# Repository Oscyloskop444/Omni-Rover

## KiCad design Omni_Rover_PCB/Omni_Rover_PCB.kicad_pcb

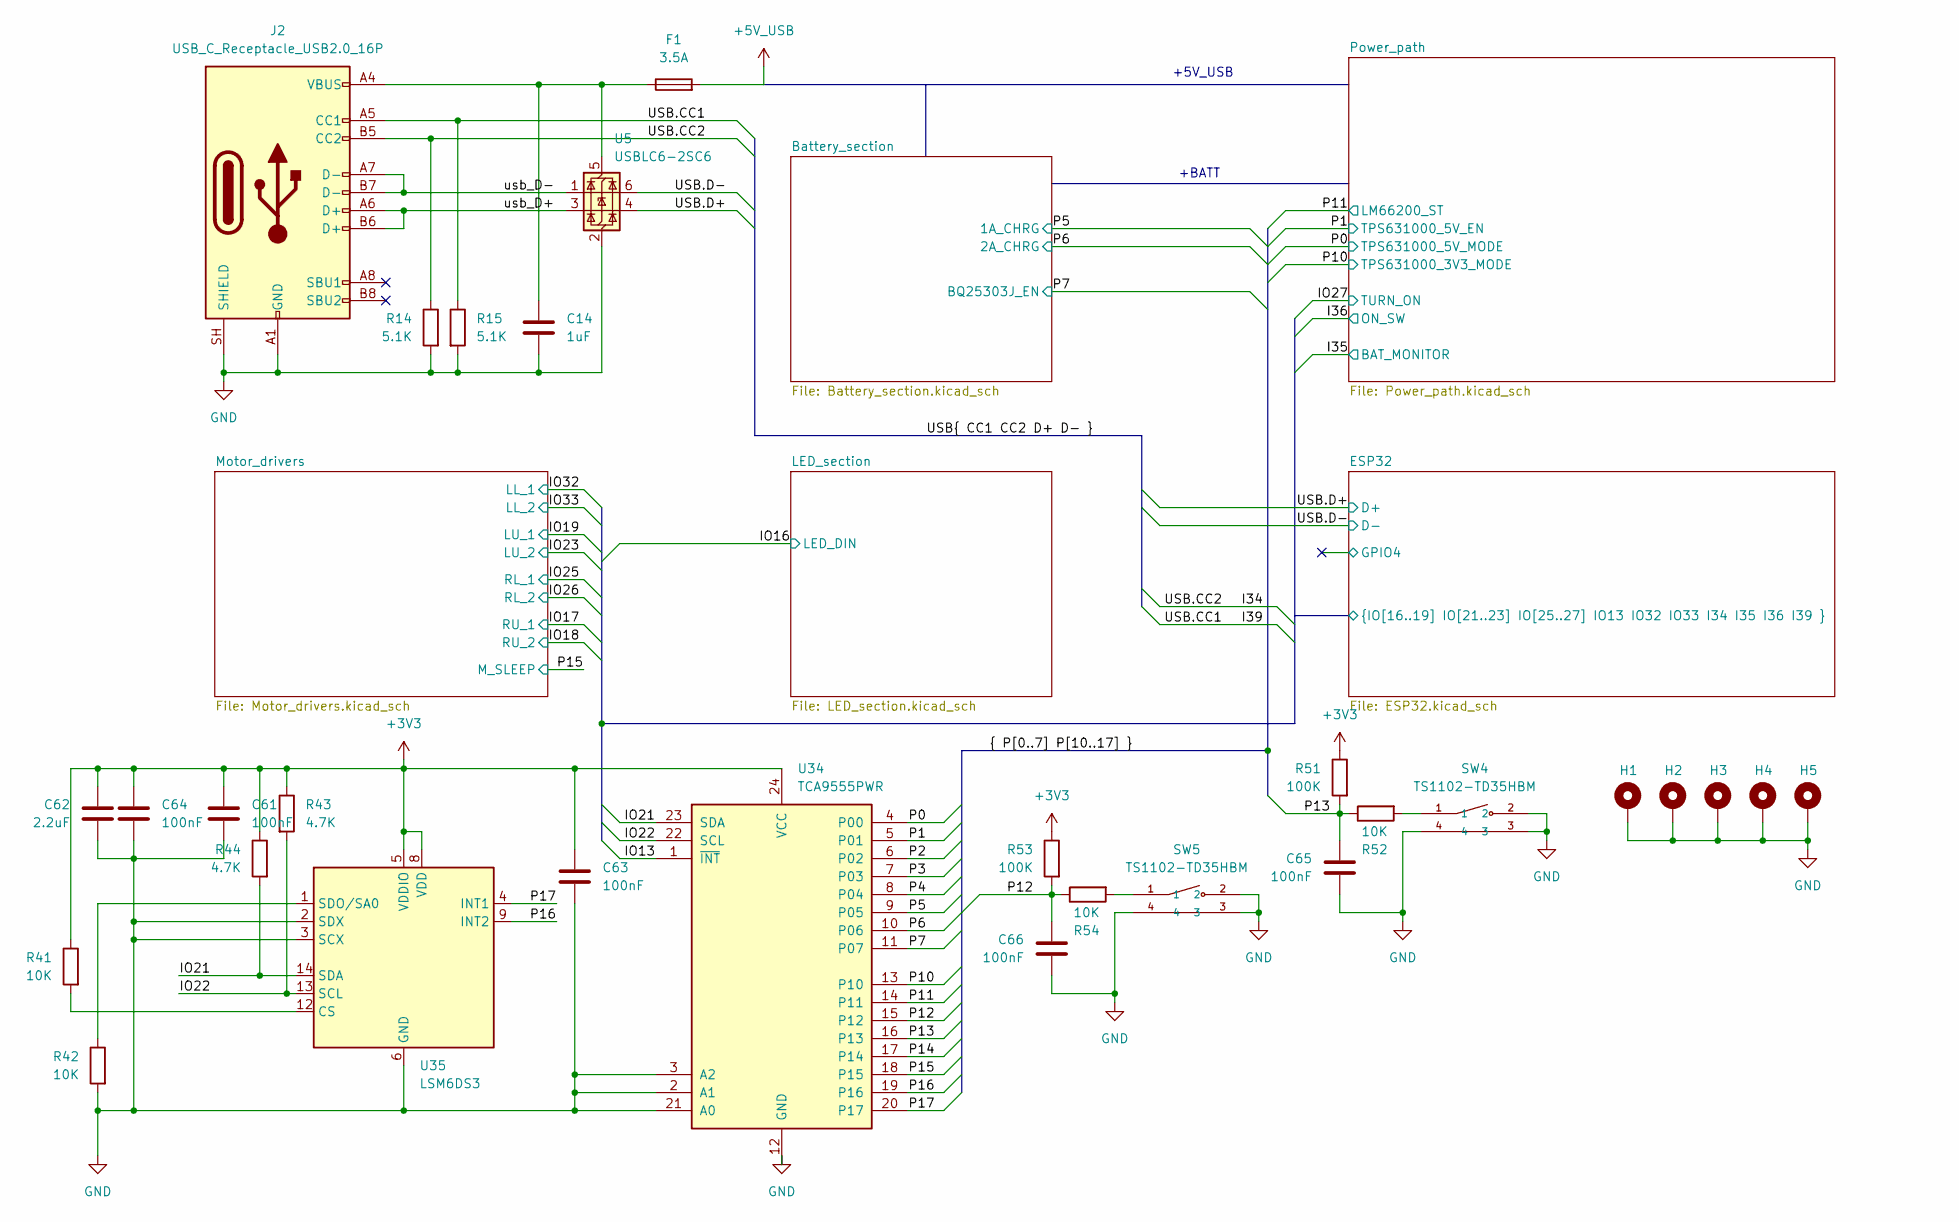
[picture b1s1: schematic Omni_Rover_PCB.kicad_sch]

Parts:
C14: 1uF; C_0603_1608Metric_Pad1.08x0.95mm_HandSolder
C61, C63, C64, C65, C66: 100nF; C_0402_1005Metric_Pad0.74x0.62mm_HandSolder
C62: 2.2uF; C_0402_1005Metric_Pad0.74x0.62mm_HandSolder
F1: 3.5A; Fuse_1206_3216Metric_Pad1.42x1.75mm_HandSolder
H1, H2, H3, H4, H5: MountingHole_Pad; MountingHole_3.2mm_M3_Pad_Via
J2: USB_C_Receptacle_USB2.0_16P; USB_C_Receptacle_GCT_USB4105-xx-A_16P_TopMnt_Horizontal
R14, R15: 5.1K; R_0402_1005Metric_Pad0.72x0.64mm_HandSolder
R41, R42, R52, R54: 10K; R_0402_1005Metric_Pad0.72x0.64mm_HandSolder
R43, R44: 4.7K; R_0402_1005Metric_Pad0.72x0.64mm_HandSolder
R51, R53: 100K; R_0402_1005Metric_Pad0.72x0.64mm_HandSolder
SW4, SW5: TS1102-TD35HBM; C36936640_SW-SMD_TS1102-TD35HBM; LCSC C36936640
U5: USBLC6-2SC6; SOT-23-6
U34: TCA9555PWR; TSSOP-24_4.4x7.8mm_P0.65mm
U35: LSM6DS3; LGA-14_3x2.5mm_P0.5mm_LayoutBorder3x4y

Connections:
+3V3: C61.2, C62.1, C63.2, C64.2, R41.1, R43.1, R44.1, R51.1, R53.1, U34.24 (VCC), U35.5 (VDDIO), U35.8 (VDD); also elsewhere on the board
+5V_USB: F1.2; also elsewhere on the board
/ESP32/I34: J2.B5 (CC2), R14.1; also elsewhere on the board
/ESP32/I39: J2.A5 (CC1), R15.1; also elsewhere on the board
/ESP32/IO13: U34.1 (~INT); also elsewhere on the board
/ESP32/IO21: R44.2, U34.23 (SDA), U35.14 (SDA); also elsewhere on the board
/ESP32/IO22: R43.2, U34.22 (SCL), U35.13 (SCL); also elsewhere on the board
/P0: U34.4 (P00); also elsewhere on the board
/P1: U34.5 (P01); also elsewhere on the board
/P2: U34.6 (P02)
/P3: U34.7 (P03)
/P4: U34.8 (P04)
/P5: U34.9 (P05); also elsewhere on the board
/P6: U34.10 (P06); also elsewhere on the board
/P7: U34.11 (P07); also elsewhere on the board
/P10: U34.13 (P10); also elsewhere on the board
/P11: U34.14 (P11); also elsewhere on the board
/P12: C66.2, R53.2, R54.1, U34.15 (P12)
/P13: C65.2, R51.2, R52.1, U34.16 (P13)
/P14: U34.17 (P14)
/P15: U34.18 (P15); also elsewhere on the board
/P16: U34.19 (P16), U35.9 (INT2)
/P17: U34.20 (P17), U35.4 (INT1)
/USB.D+: U5.4 (I/O2); also elsewhere on the board
/USB.D-: U5.6 (I/O1); also elsewhere on the board
/usb_D+: J2.A6 (D+), J2.B6 (D+), U5.3 (I/O2)
/usb_D-: J2.A7 (D-), J2.B7 (D-), U5.1 (I/O1)
GND: C14.2, C61.1, C62.2, C63.1, C64.1, C65.1, C66.1, H1.1 (1_1), H2.1 (1_1), H3.1 (1_1), H4.1 (1_1), H5.1 (1_1), J2.A1 (GND), J2.A12 (GND), J2.B1 (GND), J2.B12 (GND), J2.SH (SHIELD), R14.2, R15.2, R42.2, SW4.2, SW4.3, SW4.4, SW5.2, SW5.3, SW5.4, U5.2 (GND), U34.2 (A1), U34.3 (A2), U34.12 (GND), U34.21 (A0), U35.2 (SDX), U35.3 (SCX), U35.6 (GND), U35.7 (GND); also elsewhere on the board
unnamed: R52.2, SW4.1
unnamed: R54.2, SW5.1
unnamed: C14.1, F1.1, J2.A4 (VBUS), J2.A9 (VBUS), J2.B4 (VBUS), J2.B9 (VBUS), U5.5 (VBUS)
unnamed: R41.2, U35.12 (CS)
unnamed: R42.1, U35.1 (SDO/SA0)

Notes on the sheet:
+BATT
+5V_USB

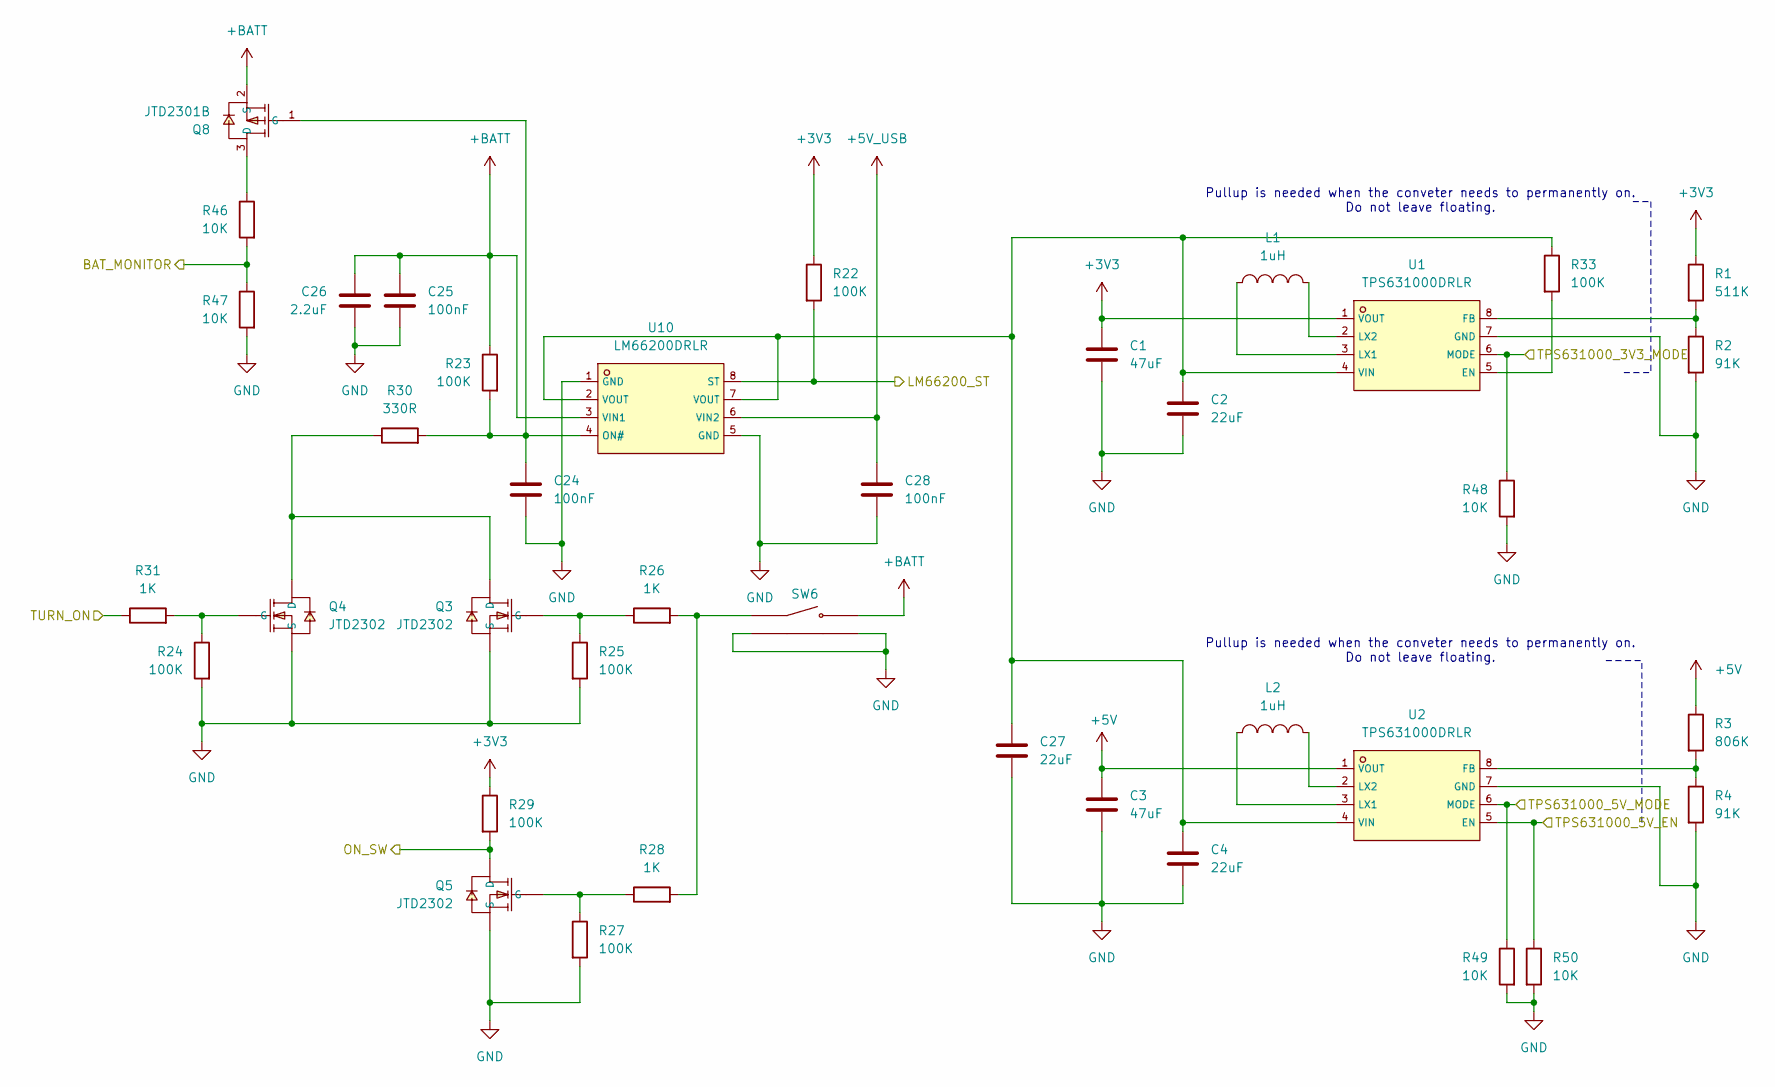
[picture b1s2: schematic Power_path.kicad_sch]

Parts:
C1, C3: 47uF; C_0805_2012Metric_Pad1.18x1.45mm_HandSolder
C2, C4: 22uF; C_0603_1608Metric_Pad1.08x0.95mm_HandSolder
C24, C25, C28: 100nF; C_0402_1005Metric_Pad0.74x0.62mm_HandSolder
C26: 2.2uF; C_0402_1005Metric_Pad0.74x0.62mm_HandSolder
C27: 22uF; C_0805_2012Metric_Pad1.18x1.45mm_HandSolder
L1, L2: 1uH; C882955_L1008; LCSC C882955
Q3, Q4, Q5: JTD2302; C42443455_SOT-23-3_L2_9-W1_5-P2_0-LS2_5-BR; LCSC C42443455
Q8: JTD2301B; C49308281_SOT-23-3_L2_9-W1_3-P1_90-LS2_4-BR; LCSC C49308281
R1: 511K; R_0402_1005Metric_Pad0.72x0.64mm_HandSolder
R2, R4: 91K; R_0402_1005Metric_Pad0.72x0.64mm_HandSolder
R3: 806K; R_0402_1005Metric_Pad0.72x0.64mm_HandSolder
R22, R23, R24, R25, R27, R29, R33: 100K; R_0402_1005Metric_Pad0.72x0.64mm_HandSolder
R26, R28, R31: 1K; R_0402_1005Metric_Pad0.72x0.64mm_HandSolder
R30: 330R; R_0402_1005Metric_Pad0.72x0.64mm_HandSolder
R46, R47, R48, R49, R50: 10K; R_0402_1005Metric_Pad0.72x0.64mm_HandSolder
SW6: TS1102-TD35HBM; C36936640_SW-SMD_TS1102-TD35HBM; LCSC C36936640
U1, U2: TPS631000DRLR; C5219190_SOT-583-8_L2_1-W1_2-P0_50-LS1_6-BL; LCSC C5219190
U10: LM66200DRLR; C3235556_SOT-583-8_L2_1-W1_2-P0_50-LS1_6-BL; LCSC C3235556

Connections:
+3V3: C1.1, R1.1, R22.1, R29.1, U1.1 (VOUT); also elsewhere on the board
+5V: C3.1, R3.1, U2.1 (VOUT); also elsewhere on the board
+5V_USB: C28.1, U10.6 (VIN2); also elsewhere on the board
+BATT: C25.1, C26.1, Q8.2 (S), R23.1, SW6.2, U10.3 (VIN1); also elsewhere on the board
/ESP32/I35: R46.2, R47.1; also elsewhere on the board
/ESP32/I36: Q5.3 (D), R29.2; also elsewhere on the board
/ESP32/IO27: R31.1; also elsewhere on the board
/P0: R49.1, U2.6 (MODE); also elsewhere on the board
/P1: R50.1, U2.5 (EN); also elsewhere on the board
/P10: R48.1, U1.6 (MODE); also elsewhere on the board
/P11: R22.2, U10.8 (ST); also elsewhere on the board
GND: C1.2, C2.2, C3.2, C4.2, C24.2, C25.2, C26.2, C27.2, C28.2, Q3.2 (S), Q4.2 (S), Q5.2 (S), R2.2, R4.2, R24.2, R25.2, R27.2, R47.2, R48.2, R49.2, R50.2, SW6.3, SW6.4, U1.7 (GND), U2.7 (GND), U10.1 (GND), U10.5 (GND); also elsewhere on the board
unnamed: Q3.3 (D), Q4.3 (D), R30.1
unnamed: Q3.1 (G), R25.1, R26.1
unnamed: Q4.1 (G), R24.1, R31.2
unnamed: Q5.1 (G), R27.1, R28.1
unnamed: Q8.3 (D), R46.1
unnamed: C24.1, Q8.1 (G), R23.2, R30.2, U10.4 (ON#)
unnamed: R26.2, R28.2, SW6.1
unnamed: R33.2, U1.5 (EN)
unnamed: R1.2, R2.1, U1.8 (FB)
unnamed: L1.1, U1.3 (LX1)
unnamed: L1.2, U1.2 (LX2)
unnamed: C2.1, C4.1, C27.1, R33.1, U1.4 (VIN), U2.4 (VIN), U10.2 (VOUT), U10.7 (VOUT)
unnamed: R3.2, R4.1, U2.8 (FB)
unnamed: L2.1, U2.3 (LX1)
unnamed: L2.2, U2.2 (LX2)

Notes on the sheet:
Pullup is needed when the conveter needs to permanently on. Do not leave floating.

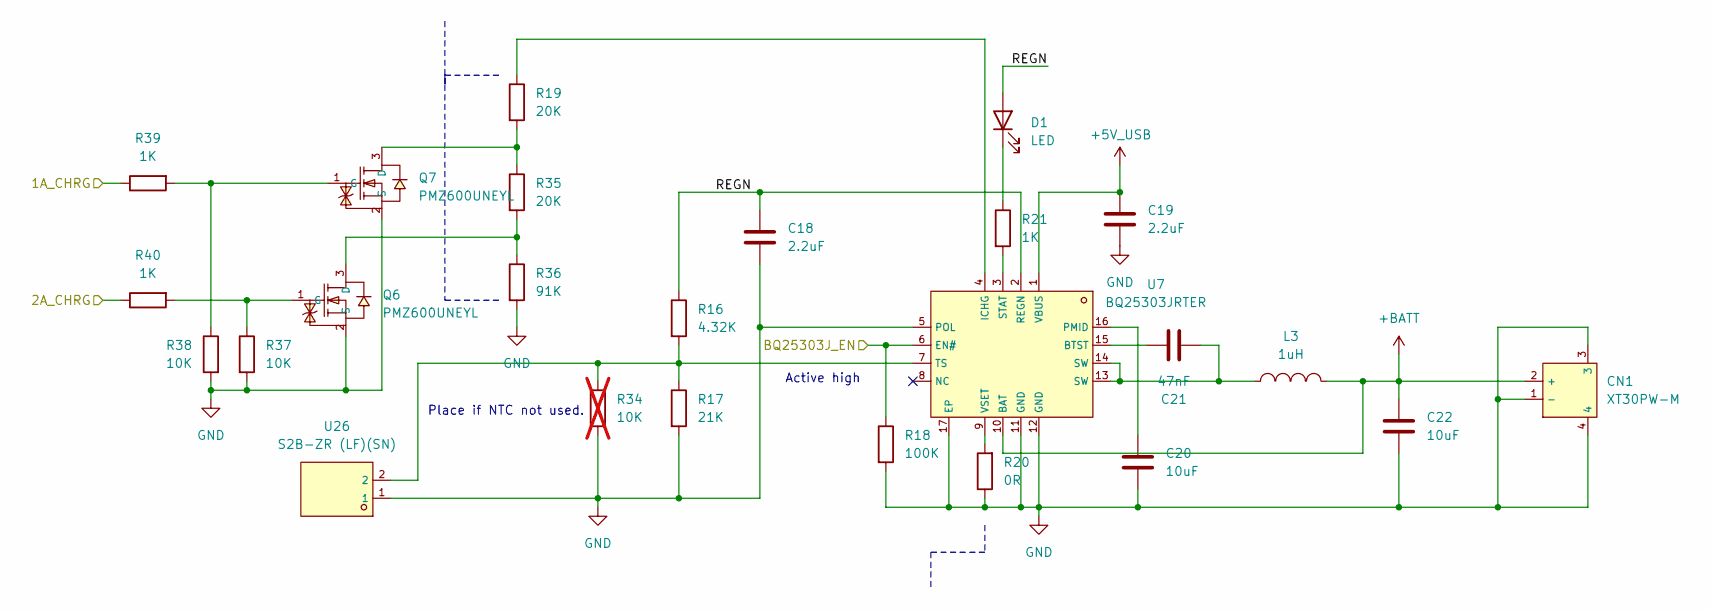
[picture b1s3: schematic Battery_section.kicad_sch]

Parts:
C18, C19: 2.2uF; C_0603_1608Metric_Pad1.08x0.95mm_HandSolder
C20, C22: 10uF; C_0805_2012Metric_Pad1.18x1.45mm_HandSolder
C21: 47nF; C_0402_1005Metric_Pad0.74x0.62mm_HandSolder
CN1: XT30PW-M; C431092_CONN-TH_XT30PW-M; LCSC C431092
D1: LED; LED_0805_2012Metric_Pad1.15x1.40mm_HandSolder
L3: 1uH; C135261_IND-SMD_L4_0-W4_0_SMNR4020; LCSC C135261
Q6, Q7: PMZ600UNEYL; C547286_SOT-883-3_L1_0-W0_6-BR; LCSC C547286
R16: 4.32K; R_0402_1005Metric_Pad0.72x0.64mm_HandSolder
R17: 21K; R_0402_1005Metric_Pad0.72x0.64mm_HandSolder
R18: 100K; R_0402_1005Metric_Pad0.72x0.64mm_HandSolder
R19, R35: 20K; R_0402_1005Metric_Pad0.72x0.64mm_HandSolder
R20: 0R; R_0402_1005Metric_Pad0.72x0.64mm_HandSolder
R21, R39, R40: 1K; R_0402_1005Metric_Pad0.72x0.64mm_HandSolder
R34: 10K; R_0402_1005Metric_Pad0.72x0.64mm_HandSolder; not fitted
R36: 91K; R_0402_1005Metric_Pad0.72x0.64mm_HandSolder
R37, R38: 10K; R_0402_1005Metric_Pad0.72x0.64mm_HandSolder
U7: BQ25303JRTER; C2842775_WQFN-16_L3_0-W3_0-P0_50-BL-EP1_7; LCSC C2842775
U26: S2B-ZR (LF)(SN); C157930_CONN-TH_S2B-ZR-LF-SN; LCSC C157930

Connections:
+5V_USB: C19.1, U7.1 (VBUS); also elsewhere on the board
+BATT: C22.1, CN1.2 (+), L3.2, U7.10 (BAT); also elsewhere on the board
/Battery_section/REGN: C18.1, D1.2 (A), R16.1, U7.2 (REGN)
/P5: R39.1; also elsewhere on the board
/P6: R40.1; also elsewhere on the board
/P7: R18.1, U7.6 (EN#); also elsewhere on the board
GND: C18.2, C19.2, C20.2, C22.2, CN1.1 (-), CN1.3, CN1.4, Q6.2 (S), Q7.2 (S), R17.2, R18.2, R20.1, R34.2, R36.2, R37.2, R38.2, U7.5 (POL), U7.11 (GND), U7.12 (GND), U7.17 (EP), U26.1; also elsewhere on the board
unnamed: C21.1, L3.1, U7.13 (SW), U7.14 (SW)
unnamed: D1.1 (K), R21.1
unnamed: Q6.3 (D), R35.2, R36.1
unnamed: Q6.1 (G), R37.1, R40.2
unnamed: Q7.3 (D), R19.2, R35.1
unnamed: Q7.1 (G), R38.1, R39.2
unnamed: C21.2, U7.15 (BTST)
unnamed: R19.1, U7.4 (ICHG)
unnamed: C20.1, U7.16 (PMID)
unnamed: R21.2, U7.3 (STAT)
unnamed: R16.2, R17.1, R34.1, U7.7 (TS), U26.2
unnamed: R20.2, U7.9 (VSET)

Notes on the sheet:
Place if NTC not used.
Active high

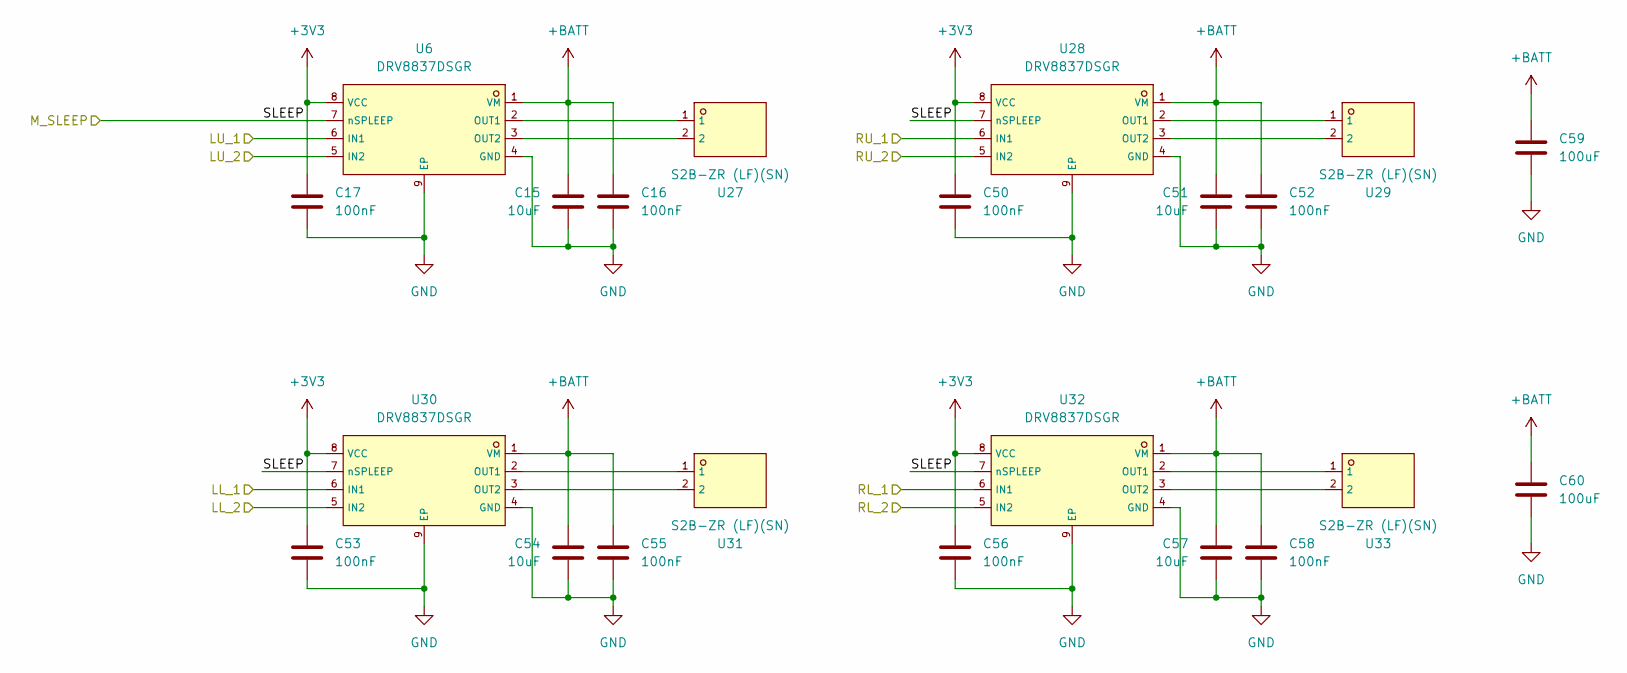
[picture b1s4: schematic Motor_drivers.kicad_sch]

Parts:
C15, C51, C54, C57: 10uF; C_0805_2012Metric_Pad1.18x1.45mm_HandSolder
C16, C17, C50, C52, C53, C55, C56, C58: 100nF; C_0402_1005Metric_Pad0.74x0.62mm_HandSolder
C59, C60: 100uF; C_1206_3216Metric_Pad1.33x1.80mm_HandSolder
U6, U28, U30, U32: DRV8837DSGR; C39159_WSON-8_L2_0-W2_0-P0_50-TL-EP; LCSC C39159
U27, U29, U31, U33: S2B-ZR (LF)(SN); C157930_CONN-TH_S2B-ZR-LF-SN; LCSC C157930

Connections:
+3V3: C17.1, C50.1, C53.1, C56.1, U6.8 (VCC), U28.8 (VCC), U30.8 (VCC), U32.8 (VCC); also elsewhere on the board
+BATT: C15.1, C16.1, C51.1, C52.1, C54.1, C55.1, C57.1, C58.1, C59.1, C60.1, U6.1 (VM), U28.1 (VM), U30.1 (VM), U32.1 (VM); also elsewhere on the board
/ESP32/IO17: U28.6 (IN1); also elsewhere on the board
/ESP32/IO18: U28.5 (IN2); also elsewhere on the board
/ESP32/IO19: U6.6 (IN1); also elsewhere on the board
/ESP32/IO23: U6.5 (IN2); also elsewhere on the board
/ESP32/IO25: U32.6 (IN1); also elsewhere on the board
/ESP32/IO26: U32.5 (IN2); also elsewhere on the board
/ESP32/IO32: U30.6 (IN1); also elsewhere on the board
/ESP32/IO33: U30.5 (IN2); also elsewhere on the board
/P15: U6.7 (nSPLEEP), U28.7 (nSPLEEP), U30.7 (nSPLEEP), U32.7 (nSPLEEP); also elsewhere on the board
GND: C15.2, C16.2, C17.2, C50.2, C51.2, C52.2, C53.2, C54.2, C55.2, C56.2, C57.2, C58.2, C59.2, C60.2, U6.4 (GND), U6.9 (EP), U28.4 (GND), U28.9 (EP), U30.4 (GND), U30.9 (EP), U32.4 (GND), U32.9 (EP); also elsewhere on the board
unnamed: U6.2 (OUT1), U27.1
unnamed: U6.3 (OUT2), U27.2
unnamed: U28.2 (OUT1), U29.1
unnamed: U28.3 (OUT2), U29.2
unnamed: U30.2 (OUT1), U31.1
unnamed: U30.3 (OUT2), U31.2
unnamed: U32.2 (OUT1), U33.1
unnamed: U32.3 (OUT2), U33.2

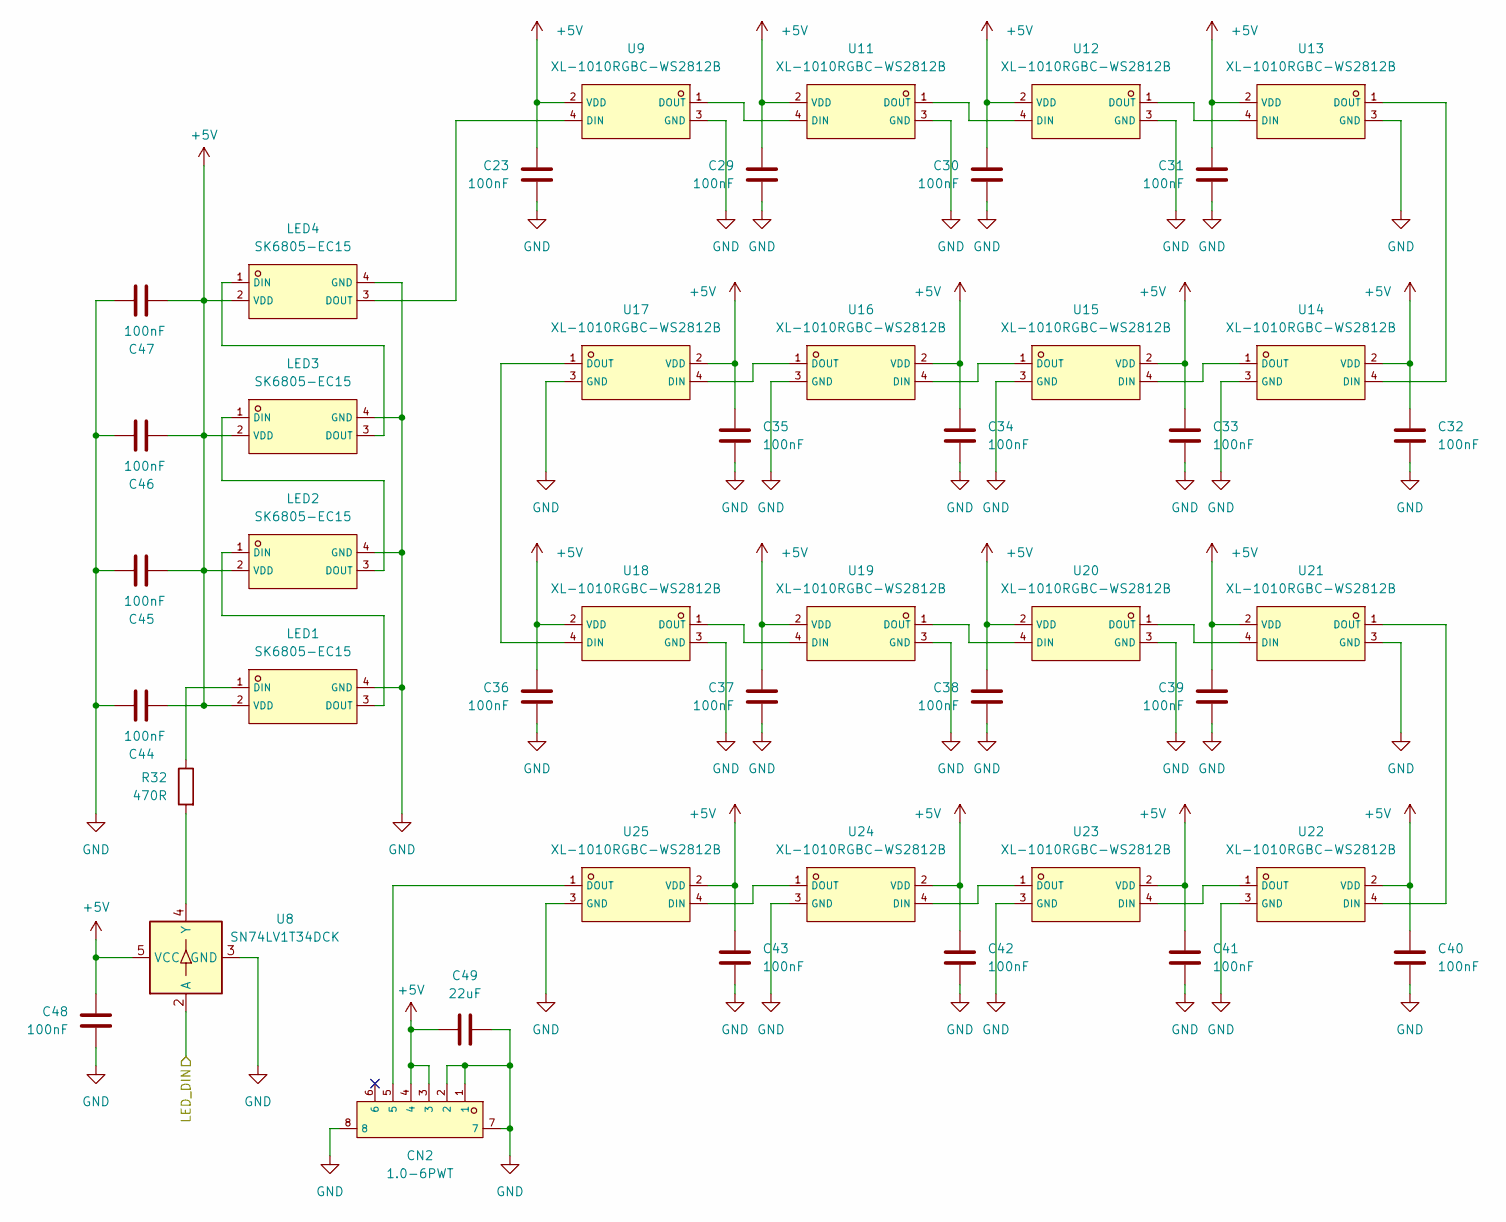
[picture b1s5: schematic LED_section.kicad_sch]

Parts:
C23, C29, C30, C31, C32, C33, C34, C35, C36, C37, C38, C39, C40, C41, C42, C43, C44, C45, C46, C47, C48: 100nF; C_0402_1005Metric_Pad0.74x0.62mm_HandSolder
C49: 22uF; C_0805_2012Metric_Pad1.18x1.45mm_HandSolder
CN2: 1.0-6PWT; C2763616_CONN-SMD_1_0-6PWT; LCSC C2763616
LED1, LED2, LED3, LED4: SK6805-EC15; C2890035_LED-SMD_4P-L1_5-W1_5-BL; LCSC C2890035
R32: 470R; R_0402_1005Metric_Pad0.72x0.64mm_HandSolder
U8: SN74LV1T34DCK; SOT-353_SC-70-5
U9, U11, U12, U13, U14, U15, U16, U17, U18, U19, U20, U21, U22, U23, U24, U25: XL-1010RGBC-WS2812B; C5349953_LED-SMD_4P-L1_0-W1_0-TL_XL-1010RGBC-WS2812B; LCSC C5349953

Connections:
+5V: C23.1, C29.1, C30.1, C31.1, C32.1, C33.1, C34.1, C35.1, C36.1, C37.1, C38.1, C39.1, C40.1, C41.1, C42.1, C43.1, C44.2, C45.2, C46.2, C47.2, C48.1, C49.1, CN2.3, CN2.4, LED1.2 (VDD), LED2.2 (VDD), LED3.2 (VDD), LED4.2 (VDD), U8.5 (VCC), U9.2 (VDD), U11.2 (VDD), U12.2 (VDD), U13.2 (VDD), U14.2 (VDD), U15.2 (VDD), U16.2 (VDD), U17.2 (VDD), U18.2 (VDD), U19.2 (VDD), U20.2 (VDD), U21.2 (VDD), U22.2 (VDD), U23.2 (VDD), U24.2 (VDD), U25.2 (VDD); also elsewhere on the board
/ESP32/IO16: U8.2 (A); also elsewhere on the board
GND: C23.2, C29.2, C30.2, C31.2, C32.2, C33.2, C34.2, C35.2, C36.2, C37.2, C38.2, C39.2, C40.2, C41.2, C42.2, C43.2, C44.1, C45.1, C46.1, C47.1, C48.2, C49.2, CN2.1, CN2.2, CN2.7, CN2.8, LED1.4 (GND), LED2.4 (GND), LED3.4 (GND), LED4.4 (GND), U8.3 (GND), U9.3 (GND), U11.3 (GND), U12.3 (GND), U13.3 (GND), U14.3 (GND), U15.3 (GND), U16.3 (GND), U17.3 (GND), U18.3 (GND), U19.3 (GND), U20.3 (GND), U21.3 (GND), U22.3 (GND), U23.3 (GND), U24.3 (GND), U25.3 (GND); also elsewhere on the board
unnamed: LED1.1 (DIN), R32.1
unnamed: LED1.3 (DOUT), LED2.1 (DIN)
unnamed: LED2.3 (DOUT), LED3.1 (DIN)
unnamed: LED3.3 (DOUT), LED4.1 (DIN)
unnamed: LED4.3 (DOUT), U9.4 (DIN)
unnamed: R32.2, U8.4 (Y)
unnamed: U9.1 (DOUT), U11.4 (DIN)
unnamed: U11.1 (DOUT), U12.4 (DIN)
unnamed: U12.1 (DOUT), U13.4 (DIN)
unnamed: U13.1 (DOUT), U14.4 (DIN)
unnamed: U14.1 (DOUT), U15.4 (DIN)
unnamed: U15.1 (DOUT), U16.4 (DIN)
unnamed: U16.1 (DOUT), U17.4 (DIN)
unnamed: U17.1 (DOUT), U18.4 (DIN)
unnamed: U18.1 (DOUT), U19.4 (DIN)
unnamed: U19.1 (DOUT), U20.4 (DIN)
unnamed: U20.1 (DOUT), U21.4 (DIN)
unnamed: U21.1 (DOUT), U22.4 (DIN)
unnamed: U22.1 (DOUT), U23.4 (DIN)
unnamed: U23.1 (DOUT), U24.4 (DIN)
unnamed: U24.1 (DOUT), U25.4 (DIN)
unnamed: CN2.5, U25.1 (DOUT)

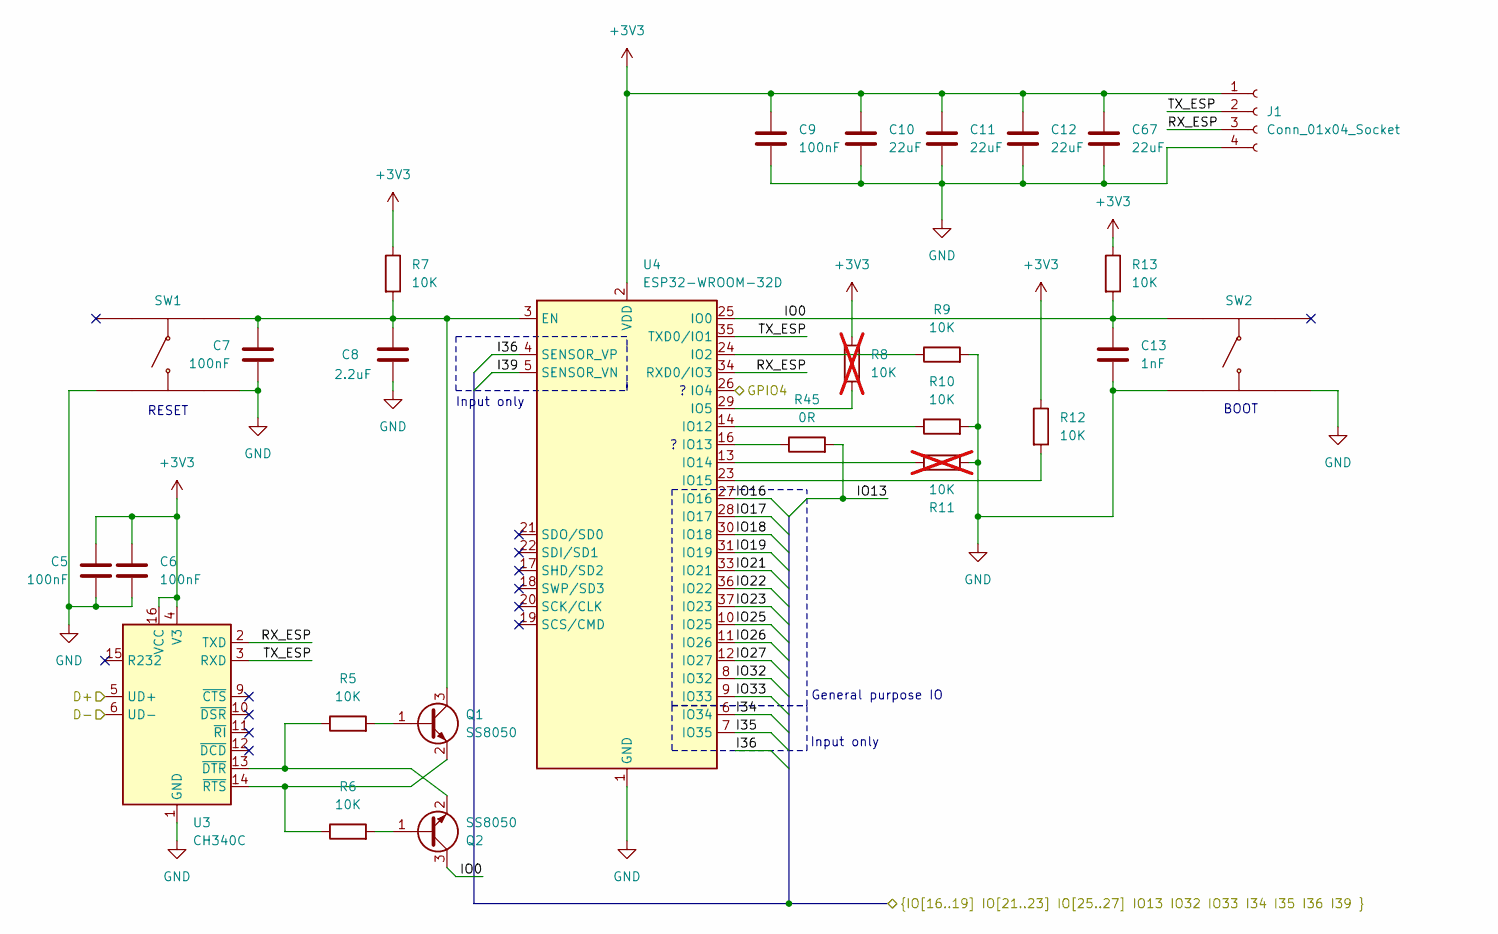
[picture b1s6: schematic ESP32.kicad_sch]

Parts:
C5, C6, C7, C9: 100nF; C_0402_1005Metric_Pad0.74x0.62mm_HandSolder
C8: 2.2uF; C_0603_1608Metric_Pad1.08x0.95mm_HandSolder
C10, C11, C12, C67: 22uF; C_0805_2012Metric_Pad1.18x1.45mm_HandSolder
C13: 1nF; C_0402_1005Metric_Pad0.74x0.62mm_HandSolder
J1: Conn_01x04_Socket; PinSocket_1x04_P2.54mm_Vertical
Q1, Q2: SS8050; SOT-23
R5, R6, R7, R9, R10, R12, R13: 10K; R_0402_1005Metric_Pad0.72x0.64mm_HandSolder
R8, R11: 10K; R_0402_1005Metric_Pad0.72x0.64mm_HandSolder; not fitted
R45: 0R; R_0402_1005Metric_Pad0.72x0.64mm_HandSolder
SW1, SW2: TSA016A2526A; C2888428_SW-SMD_4P-L4_2-W3_3-P2_15-LS4_6; LCSC C2888428
U3: CH340C; SOIC-16_3.9x9.9mm_P1.27mm
U4: ESP32-WROOM-32D

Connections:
+3V3: C5.2, C6.2, C9.1, C10.1, C11.1, C12.1, C67.1, J1.1, R7.1, R8.1, R12.1, R13.1, U3.4 (V3), U3.16 (VCC), U4.2 (VDD); also elsewhere on the board
/ESP32/GPIO4: U4.26 (IO4)
/ESP32/I34: U4.6 (IO34); also elsewhere on the board
/ESP32/I35: U4.7 (IO35); also elsewhere on the board
/ESP32/I36: U4.4 (SENSOR_VP); also elsewhere on the board
/ESP32/I39: U4.5 (SENSOR_VN); also elsewhere on the board
/ESP32/IO0: C13.2, Q2.3 (C), R13.2, SW2.1, U4.25 (IO0)
/ESP32/IO13: R45.2; also elsewhere on the board
/ESP32/IO16: U4.27 (IO16); also elsewhere on the board
/ESP32/IO17: U4.28 (IO17); also elsewhere on the board
/ESP32/IO18: U4.30 (IO18); also elsewhere on the board
/ESP32/IO19: U4.31 (IO19); also elsewhere on the board
/ESP32/IO21: U4.33 (IO21); also elsewhere on the board
/ESP32/IO22: U4.36 (IO22); also elsewhere on the board
/ESP32/IO23: U4.37 (IO23); also elsewhere on the board
/ESP32/IO25: U4.10 (IO25); also elsewhere on the board
/ESP32/IO26: U4.11 (IO26); also elsewhere on the board
/ESP32/IO27: U4.12 (IO27); also elsewhere on the board
/ESP32/IO32: U4.8 (IO32); also elsewhere on the board
/ESP32/IO33: U4.9 (IO33); also elsewhere on the board
/ESP32/RX_ESP: J1.3, U3.2 (TXD), U4.34 (RXD0/IO3)
/ESP32/TX_ESP: J1.2, U3.3 (RXD), U4.35 (TXD0/IO1)
/USB.D+: U3.5 (UD+); also elsewhere on the board
/USB.D-: U3.6 (UD-); also elsewhere on the board
GND: C5.1, C6.1, C7.1, C8.2, C9.2, C10.2, C11.2, C12.2, C13.1, C67.2, J1.4, R9.2, R10.2, R11.2, SW1.3, SW1.4, SW2.3, SW2.4, U3.1 (GND), U4.1 (GND), U4.15 (GND), U4.38 (GND), U4.39 (GND); also elsewhere on the board
unnamed: Q1.1 (B), R5.2
unnamed: C7.2, C8.1, Q1.3 (C), R7.2, SW1.2, U4.3 (EN)
unnamed: Q1.2 (E), R6.1, U3.14 (~RTS)
unnamed: Q2.1 (B), R6.2
unnamed: Q2.2 (E), R5.1, U3.13 (~DTR)
unnamed: R9.1, U4.24 (IO2)
unnamed: R8.2, U4.29 (IO5)
unnamed: R10.1, U4.14 (IO12)
unnamed: R45.1, U4.16 (IO13)
unnamed: R11.1, U4.13 (IO14)
unnamed: R12.2, U4.23 (IO15)

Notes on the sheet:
RESET
General purpose IO
BOOT
Input only

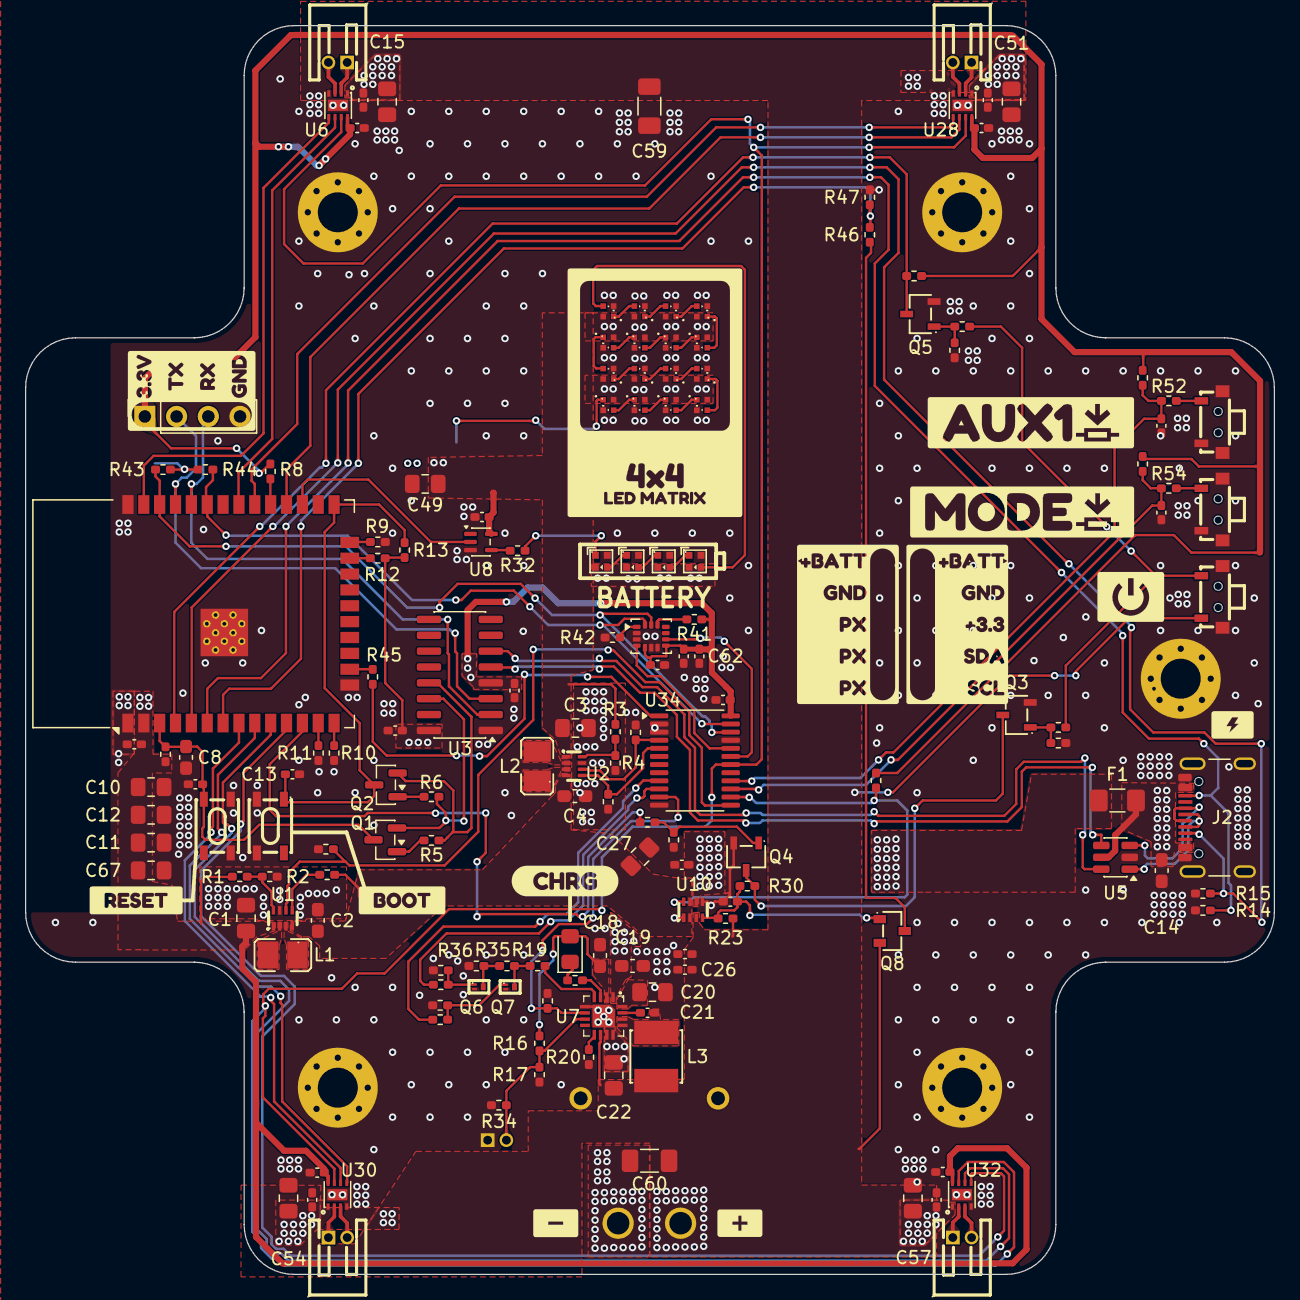
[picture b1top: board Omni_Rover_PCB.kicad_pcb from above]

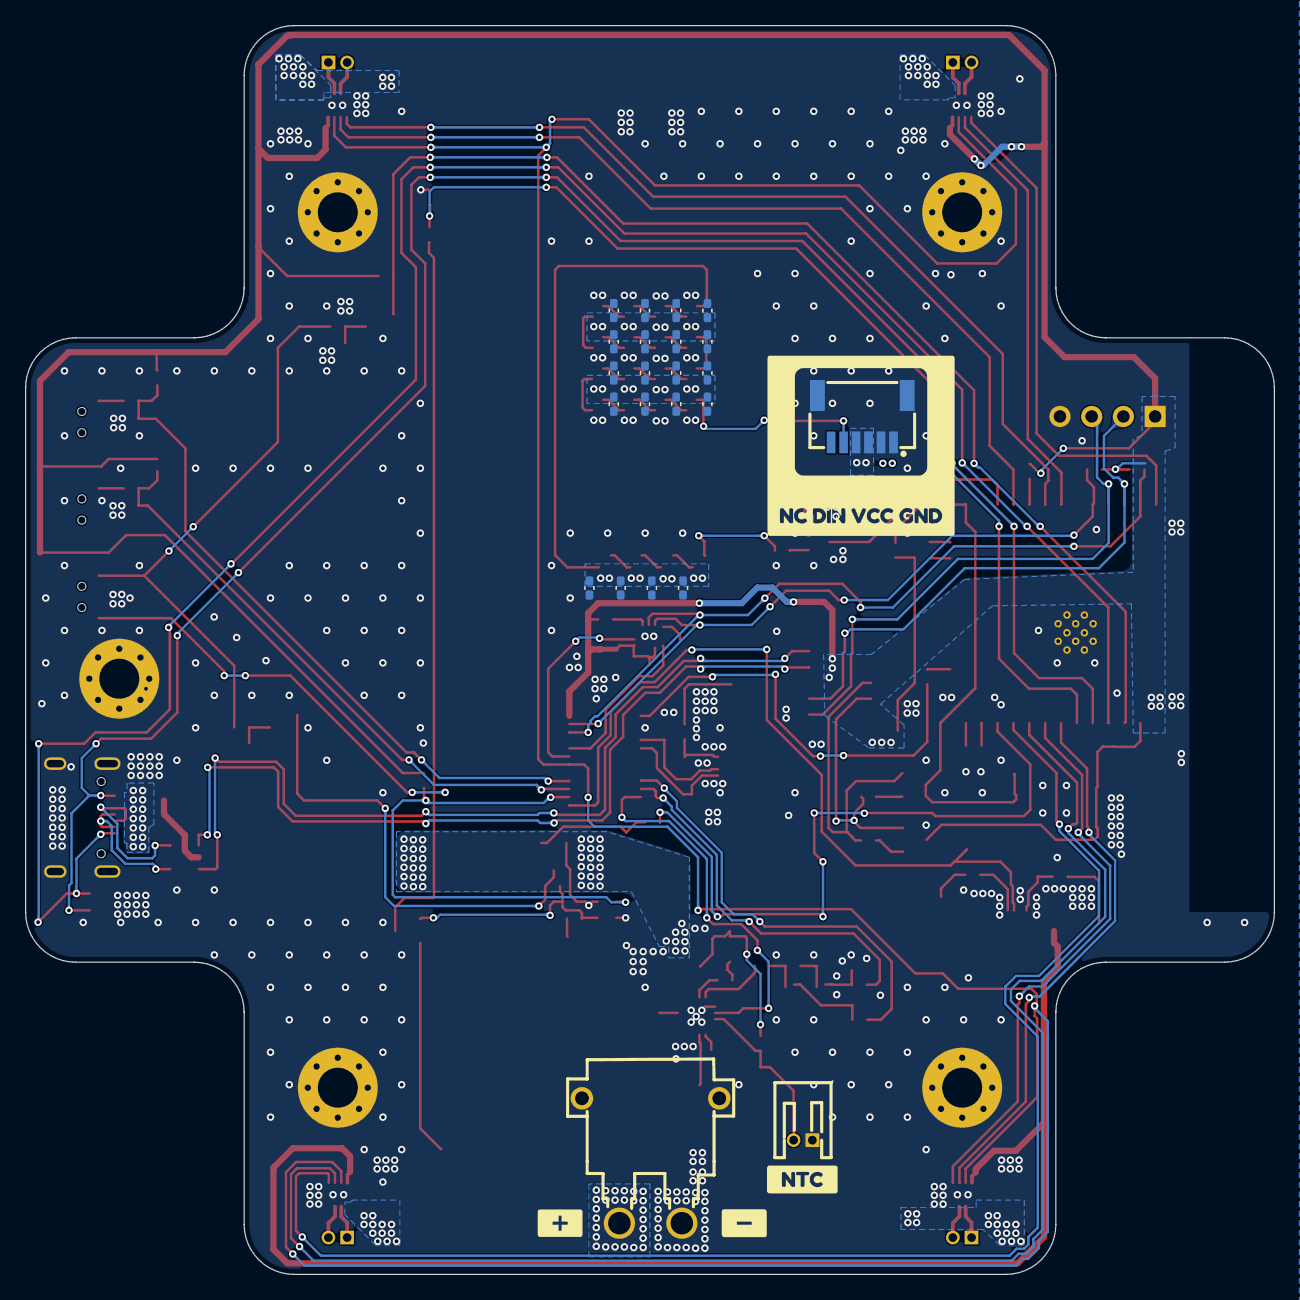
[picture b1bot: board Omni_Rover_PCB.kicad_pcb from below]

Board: 2 copper layers, 100.0 x 100.0 mm, 204 parts (27 on the bottom side), 115 nets.

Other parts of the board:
kibuzzard-6AB05A14: G***; kibuzzard-6AB05A14
kobee-studio-6AADB35F, kobee-studio-6AADB37A: Kobee Studio; kobee-studio-6AADB2AD
kobee-studio-6AB2BFE9: Kobee Studio; kobee-studio-6AB2BF39
kobee-studio-6AB5A2B4: Kobee Studio; kobee-studio-6AB5A2B4
kobee-studio-6AB5A28E: Kobee Studio; kobee-studio-6AB5A211
kobee-studio-6AB5A115: Kobee Studio; kobee-studio-6AB5A115
kobee-studio-6AB5A152: Kobee Studio; kobee-studio-6AB5A14C
kobee-studio-6AB59AC1: Kobee Studio; kobee-studio-6AB59681
kobee-studio-6AB598B2: Kobee Studio; kobee-studio-6AB598B2
kobee-studio-6AB598D9, kobee-studio-6AB598D9#2, kobee-studio-6AB59952, kobee-studio-6AB59952#2: Kobee Studio; kobee-studio-6AB598D9
kobee-studio-6AB59811, kobee-studio-6AB59858, kobee-studio-6AB59875: Kobee Studio; kobee-studio-6AB59747
